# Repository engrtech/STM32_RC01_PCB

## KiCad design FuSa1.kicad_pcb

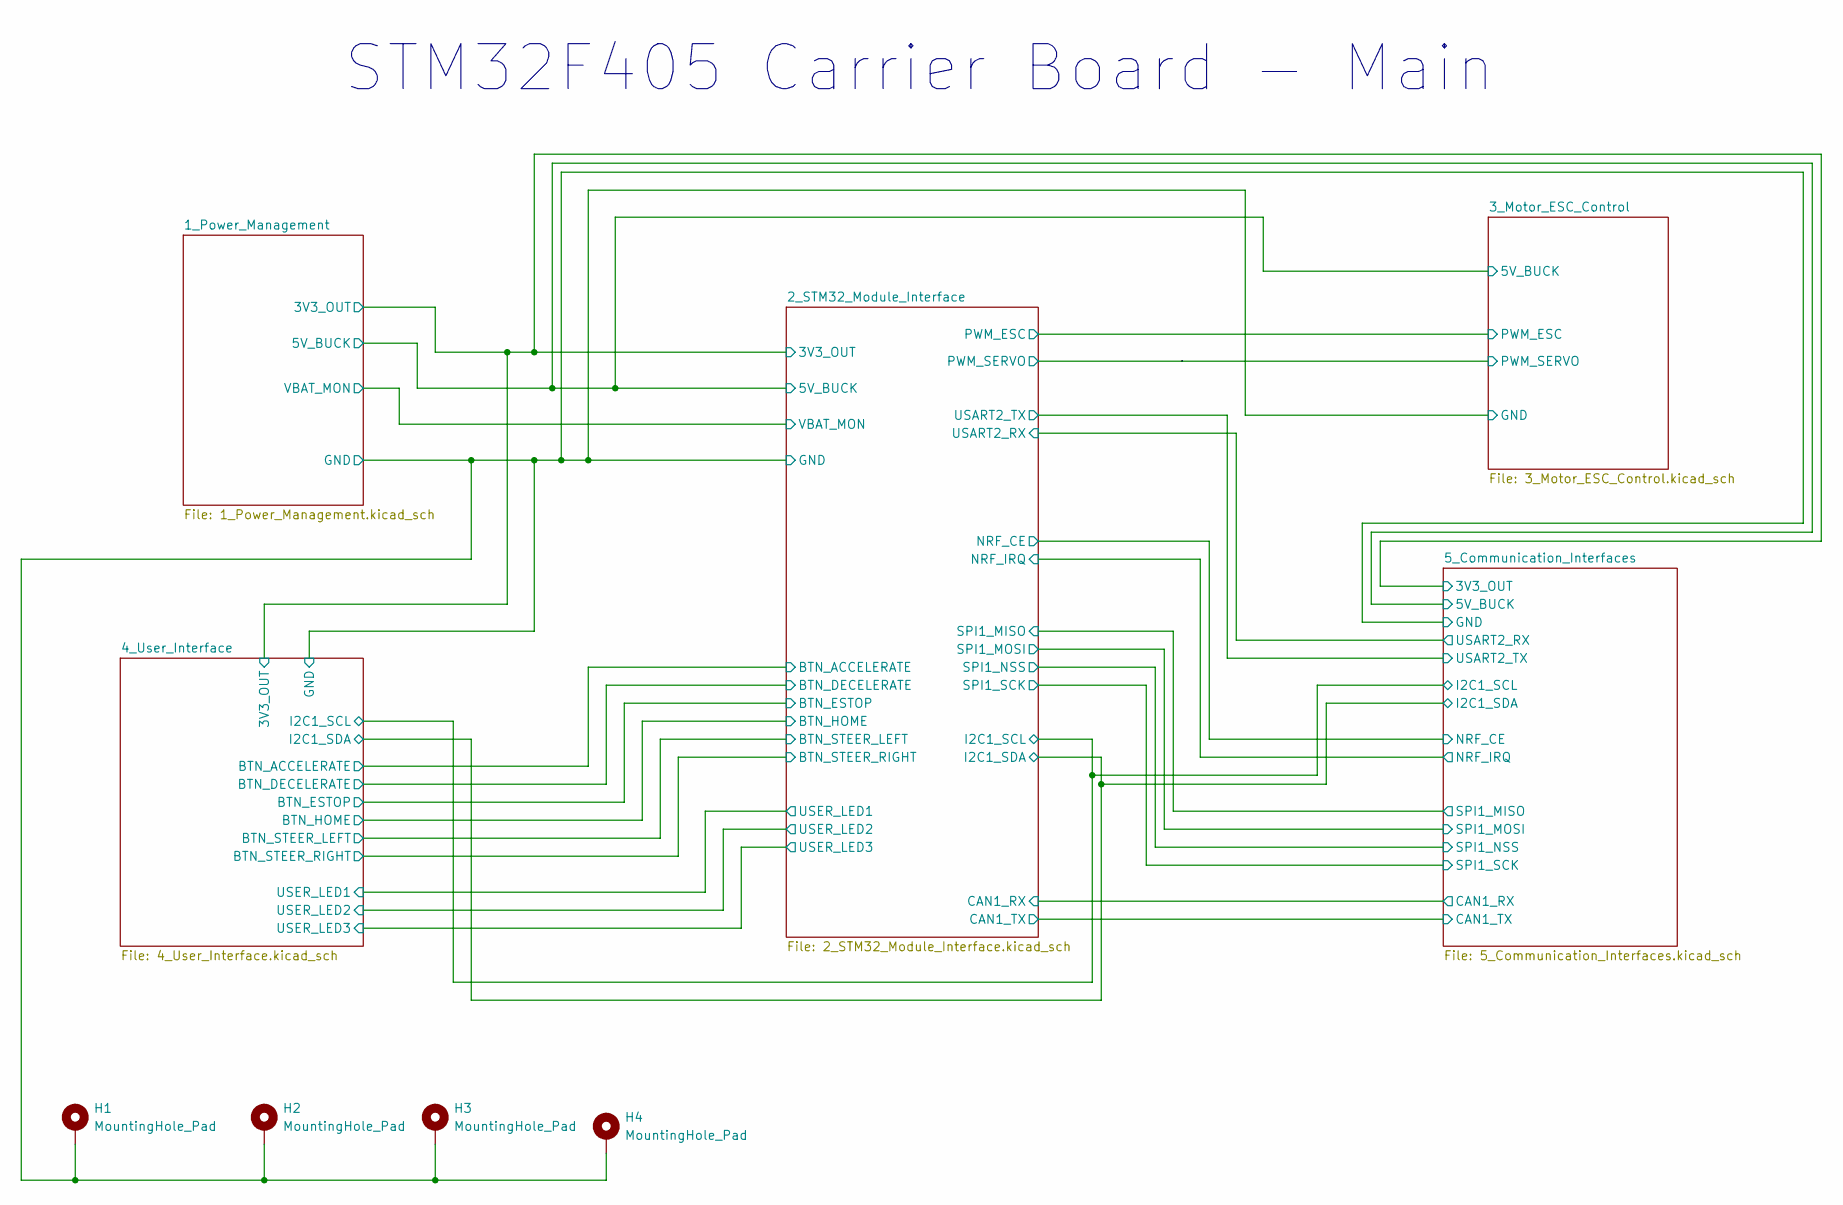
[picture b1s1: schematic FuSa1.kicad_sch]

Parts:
H1, H2, H3, H4: MountingHole_Pad; MountingHole_3.2mm_M3_Pad

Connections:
/1_Power_Management/GND: H1.1, H2.1, H3.1, H4.1; also elsewhere on the board

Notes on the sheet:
STM32F405 Carrier Board - Main

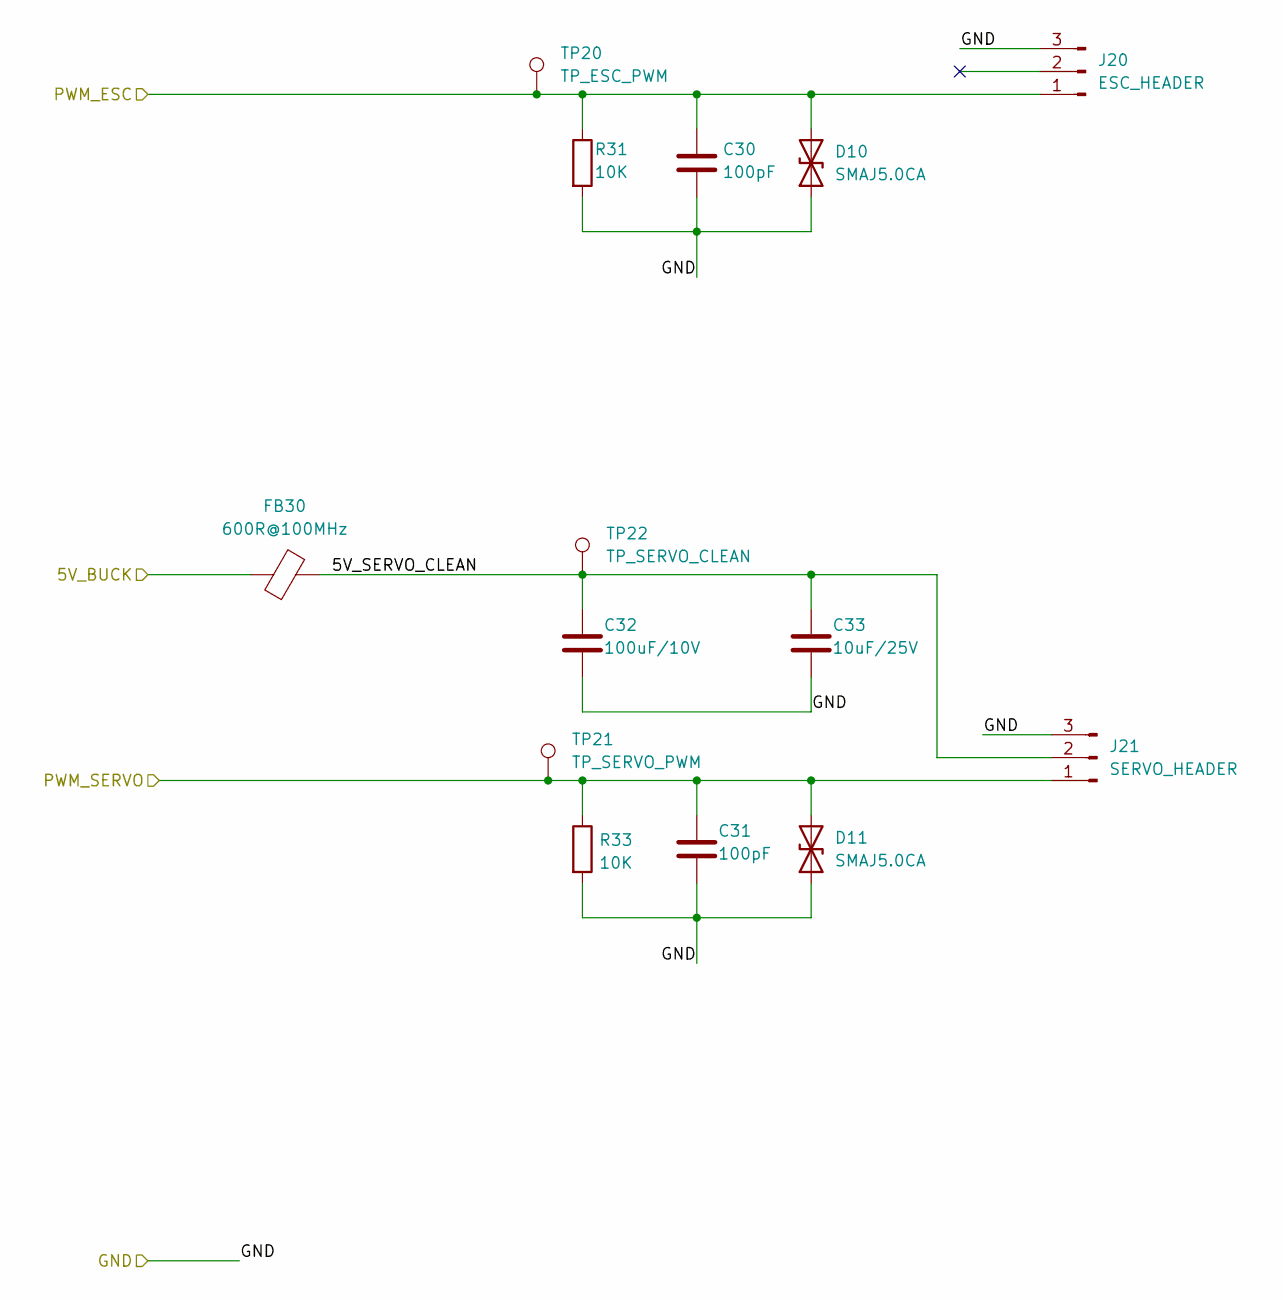
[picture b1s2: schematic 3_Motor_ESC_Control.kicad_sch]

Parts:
C30, C31: 100pF; C_0603_1608Metric; LCSC C14858
C32: 100uF/10V; CP_Radial_D5.0mm_P2.00mm; LCSC C83646
C33: 10uF/25V; C_0603_1608Metric; LCSC C6119815
D10, D11: SMAJ5.0CA; D_SMA; LCSC C83324
FB30: 600R@100MHz; L_1206_3216Metric; LCSC C16902
J20: ESC_HEADER; PinHeader_1x03_P2.54mm_Vertical
J21: SERVO_HEADER; PinHeader_1x03_P2.54mm_Vertical
R31, R33: 10K; R_0603_1608Metric; LCSC C15401
TP20: TP_ESC_PWM; TestPoint_Pad_D2.0mm
TP21: TP_SERVO_PWM; TestPoint_Pad_D2.0mm
TP22: TP_SERVO_CLEAN; TestPoint_Pad_D2.0mm

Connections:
/1_Power_Management/5V_BUCK: FB30.1; also elsewhere on the board
/1_Power_Management/GND: C30.2, C31.2, C32.2, C33.2, D10.1 (A1), D11.1 (A1), J20.3, J21.3, R31.2, R33.2; also elsewhere on the board
/2_STM32_Module_Interface/PWM_ESC: C30.1, D10.2 (A2), J20.1, R31.1, TP20.1; also elsewhere on the board
/2_STM32_Module_Interface/PWM_SERVO: C31.1, D11.2 (A2), J21.1, R33.1, TP21.1; also elsewhere on the board
/3_Motor_ESC_Control/5V_SERVO_CLEAN: C32.1, C33.1, FB30.2, J21.2, TP22.1

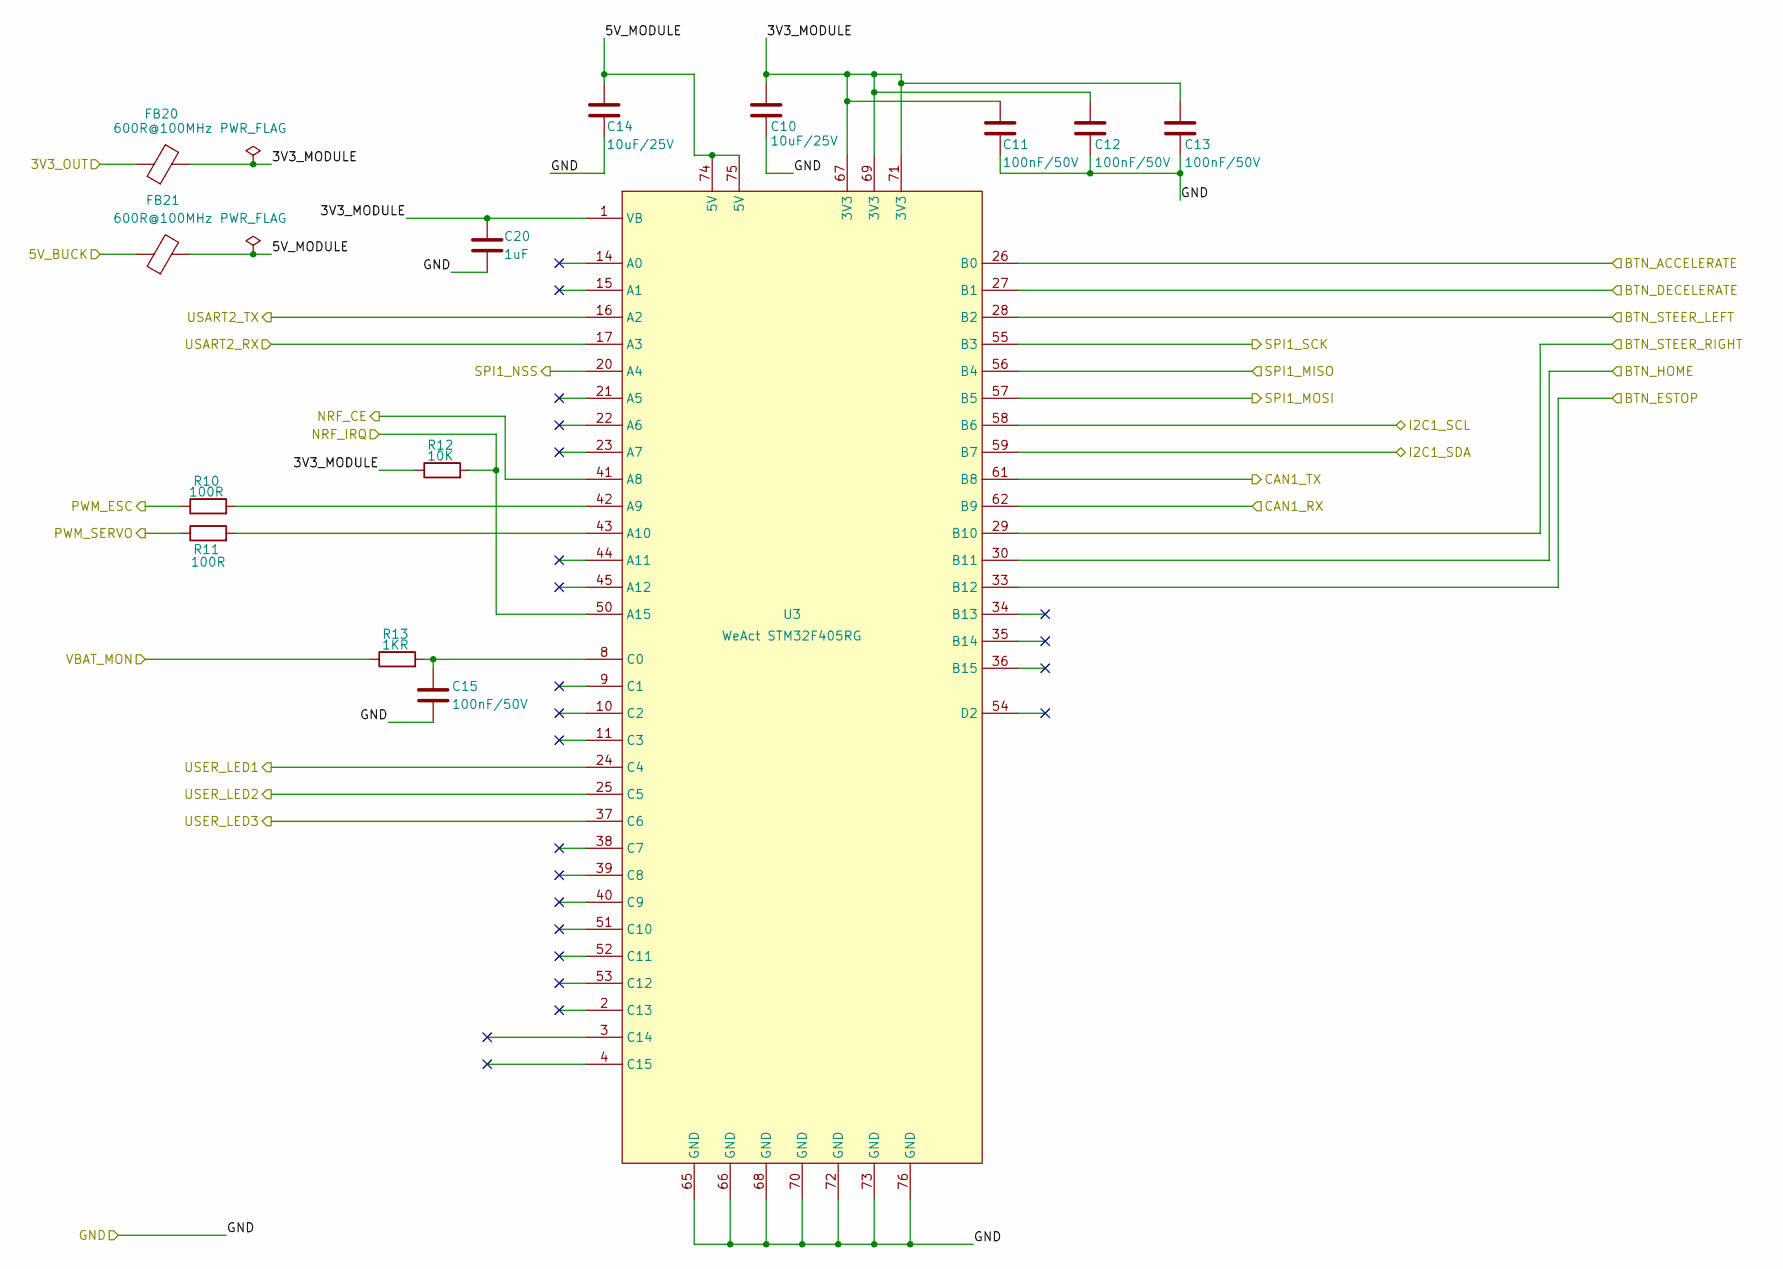
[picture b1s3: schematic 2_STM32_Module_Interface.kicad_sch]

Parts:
C10, C14: 10uF/25V; C_0603_1608Metric; LCSC C6119815
C11, C12, C13, C15: 100nF/50V; C_0603_1608Metric; LCSC C6119867
C20: 1uF; C_0603_1608Metric; LCSC C5199872
FB20, FB21: 600R@100MHz; L_1206_3216Metric; LCSC C16902
R10, R11: 100R; R_0603_1608Metric; LCSC C17901
R12: 10K; R_0603_1608Metric; LCSC C15401
R13: 1KR; R_0603_1608Metric; LCSC C14676
U3: WeAct STM32F405RG; WeAct_STM32F405

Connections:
/1_Power_Management/5V_BUCK: FB21.1; also elsewhere on the board
/1_Power_Management/GND: C10.2, C11.2, C12.2, C13.2, C14.2, C15.2, C20.1, U3.65 (GND), U3.66 (GND), U3.68 (GND), U3.70 (GND), U3.72 (GND), U3.73 (GND), U3.76 (GND); also elsewhere on the board
/1_Power_Management/VBAT_MON: R13.1; also elsewhere on the board
/2_STM32_Module_Interface/3V3_MODULE: C10.1, C11.1, C12.1, C13.1, C20.2, FB20.2, R12.1, U3.1 (VB), U3.67 (3V3), U3.69 (3V3), U3.71 (3V3)
/2_STM32_Module_Interface/5V_MODULE: C14.1, FB21.2, U3.74 (5V), U3.75 (5V)
/2_STM32_Module_Interface/BTN_ACCELERATE: U3.26 (B0); also elsewhere on the board
/2_STM32_Module_Interface/BTN_DECELERATE: U3.27 (B1); also elsewhere on the board
/2_STM32_Module_Interface/BTN_ESTOP: U3.33 (B12); also elsewhere on the board
/2_STM32_Module_Interface/BTN_HOME: U3.30 (B11); also elsewhere on the board
/2_STM32_Module_Interface/BTN_STEER_LEFT: U3.28 (B2); also elsewhere on the board
/2_STM32_Module_Interface/BTN_STEER_RIGHT: U3.29 (B10); also elsewhere on the board
/2_STM32_Module_Interface/CAN1_RX: U3.62 (B9); also elsewhere on the board
/2_STM32_Module_Interface/CAN1_TX: U3.61 (B8); also elsewhere on the board
/2_STM32_Module_Interface/NRF_CE: U3.41 (A8); also elsewhere on the board
/2_STM32_Module_Interface/NRF_IRQ: R12.2, U3.50 (A15); also elsewhere on the board
/2_STM32_Module_Interface/PWM_ESC: R10.1; also elsewhere on the board
/2_STM32_Module_Interface/PWM_SERVO: R11.1; also elsewhere on the board
/2_STM32_Module_Interface/SPI1_MISO: U3.56 (B4); also elsewhere on the board
/2_STM32_Module_Interface/SPI1_MOSI: U3.57 (B5); also elsewhere on the board
/2_STM32_Module_Interface/SPI1_NSS: U3.20 (A4); also elsewhere on the board
/2_STM32_Module_Interface/SPI1_SCK: U3.55 (B3); also elsewhere on the board
/2_STM32_Module_Interface/USER_LED1: U3.24 (C4); also elsewhere on the board
/2_STM32_Module_Interface/USER_LED2: U3.25 (C5); also elsewhere on the board
/2_STM32_Module_Interface/USER_LED3: U3.37 (C6); also elsewhere on the board
/4_User_Interface/3V3_OUT: FB20.1; also elsewhere on the board
/4_User_Interface/I2C1_SCL: U3.58 (B6); also elsewhere on the board
/4_User_Interface/I2C1_SDA: U3.59 (B7); also elsewhere on the board
/5_Communication_Interfaces/USART2_RX: U3.17 (A3); also elsewhere on the board
/5_Communication_Interfaces/USART2_TX: U3.16 (A2); also elsewhere on the board
unnamed: R10.2, U3.42 (A9)
unnamed: R11.2, U3.43 (A10)
unnamed: C15.1, R13.2, U3.8 (C0)

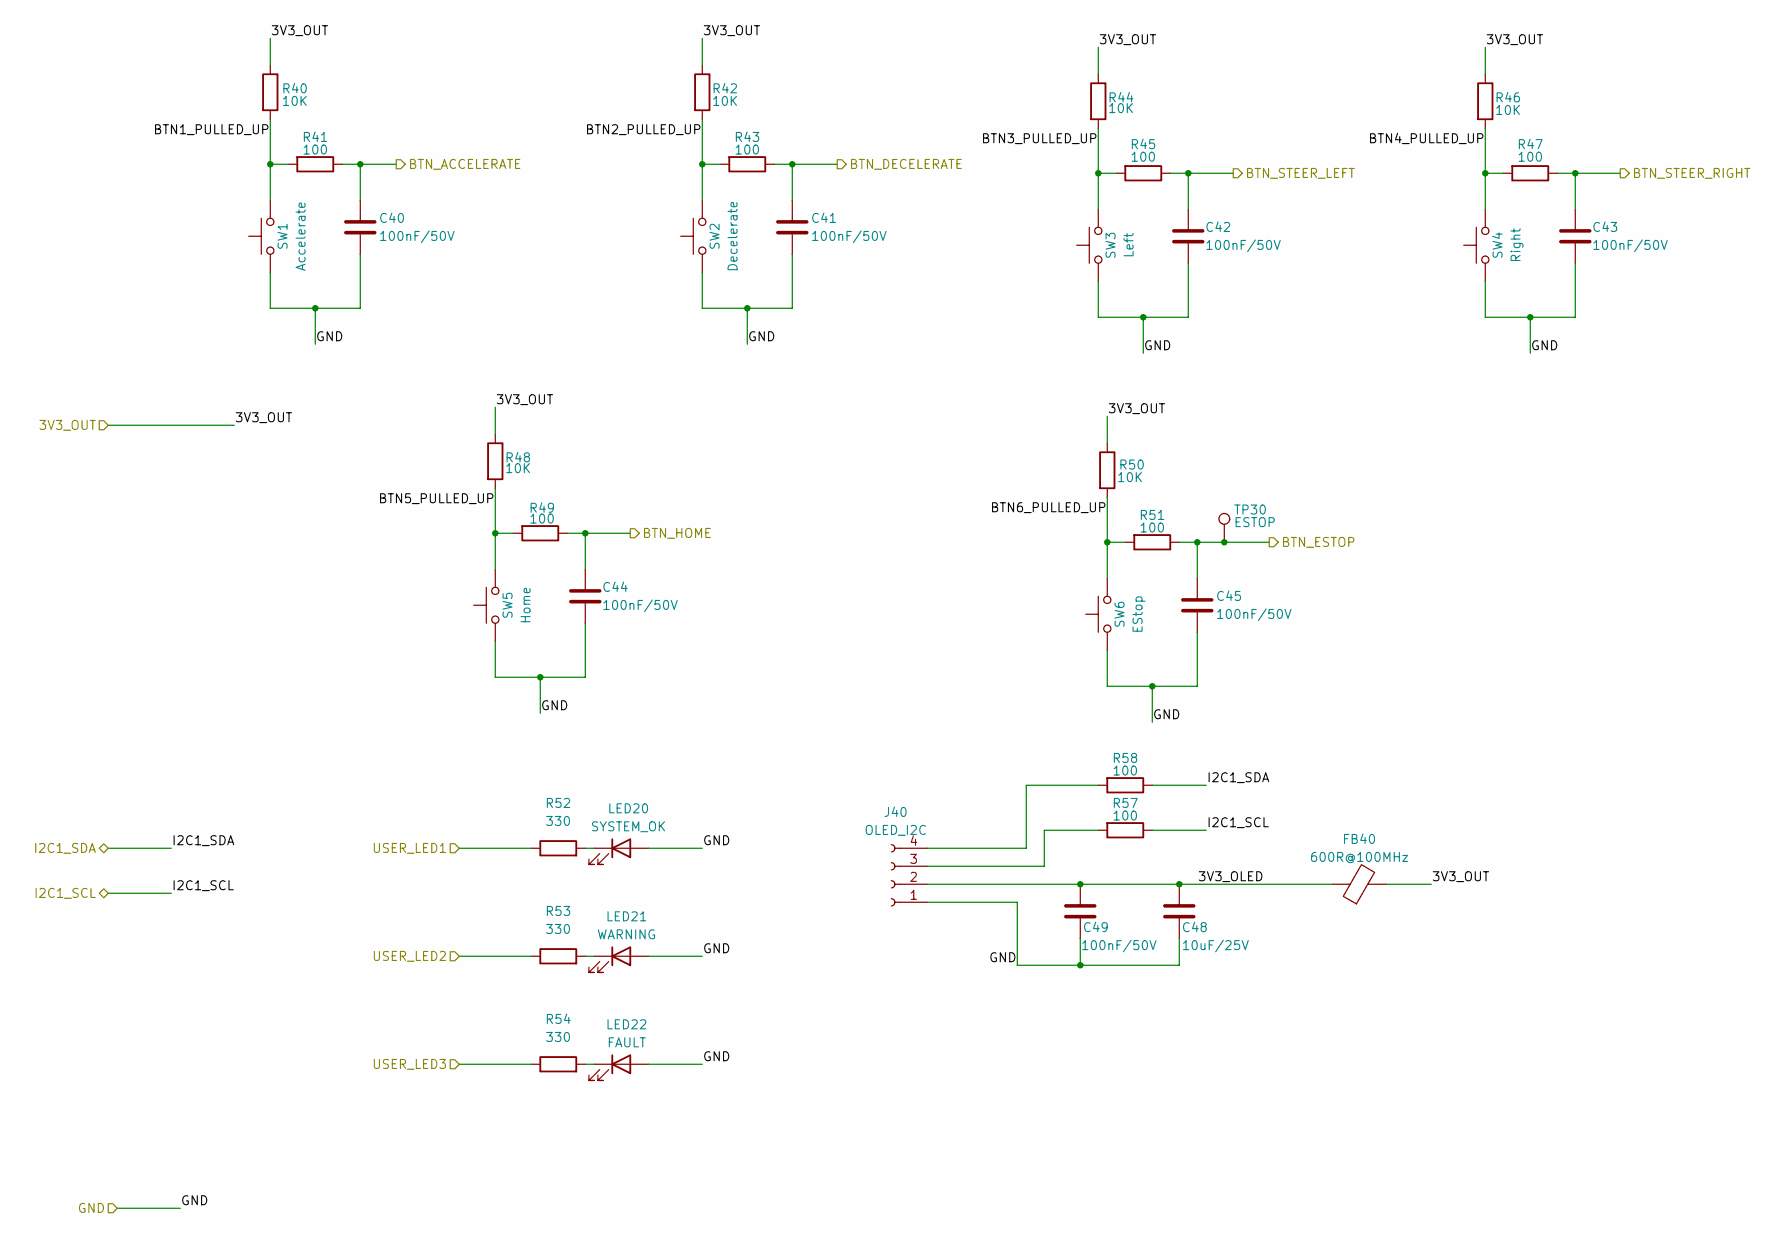
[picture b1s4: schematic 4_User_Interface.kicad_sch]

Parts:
C40, C41, C42, C43, C44, C45, C49: 100nF/50V; C_0603_1608Metric; LCSC C6119867
C48: 10uF/25V; C_0603_1608Metric; LCSC C6119815
FB40: 600R@100MHz; L_1206_3216Metric; LCSC C16902
J40: OLED_I2C; PinHeader_1x04_P2.54mm_Vertical; LCSC C124421
LED20: SYSTEM_OK; LED_1206_3216Metric; LCSC C434439
LED21: WARNING; LED_1206_3216Metric; LCSC C264322
LED22: FAULT; LED_1206_3216Metric; LCSC C559117
R40, R42, R44, R46, R48, R50: 10K; R_0603_1608Metric; LCSC C15401
R41, R43, R45, R47, R49, R51, R57, R58: 100; R_0603_1608Metric; LCSC C22775
R52, R53, R54: 330; R_0603_1608Metric; LCSC C22104
SW1: Accelerate; SW_SPST_B3U-1000P; LCSC C318884
SW2: Decelerate; SW_SPST_B3U-1000P; LCSC C318884
SW3: Left; SW_SPST_B3U-1000P; LCSC C318884
SW4: Right; SW_SPST_B3U-1000P; LCSC C318884
SW5: Home; SW_SPST_B3U-1000P; LCSC C318884
SW6: EStop; SW_SPST_B3U-1000P; LCSC C318884
TP30: ESTOP; TestPoint_Pad_D2.0mm

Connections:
/1_Power_Management/GND: C40.2, C41.2, C42.2, C43.2, C44.2, C45.2, C48.2, C49.2, J40.1, LED20.2 (A), LED21.2 (A), LED22.2 (A), SW1.1, SW2.1, SW3.1, SW4.1, SW5.1, SW6.1; also elsewhere on the board
/2_STM32_Module_Interface/BTN_ACCELERATE: C40.1, R41.1; also elsewhere on the board
/2_STM32_Module_Interface/BTN_DECELERATE: C41.1, R43.1; also elsewhere on the board
/2_STM32_Module_Interface/BTN_ESTOP: C45.1, R51.1, TP30.1; also elsewhere on the board
/2_STM32_Module_Interface/BTN_HOME: C44.1, R49.1; also elsewhere on the board
/2_STM32_Module_Interface/BTN_STEER_LEFT: C42.1, R45.1; also elsewhere on the board
/2_STM32_Module_Interface/BTN_STEER_RIGHT: C43.1, R47.1; also elsewhere on the board
/2_STM32_Module_Interface/USER_LED1: R52.1; also elsewhere on the board
/2_STM32_Module_Interface/USER_LED2: R53.1; also elsewhere on the board
/2_STM32_Module_Interface/USER_LED3: R54.1; also elsewhere on the board
/4_User_Interface/3V3_OLED: C48.1, C49.1, FB40.1, J40.2
/4_User_Interface/3V3_OUT: FB40.2, R40.1, R42.1, R44.1, R46.1, R48.1, R50.1; also elsewhere on the board
/4_User_Interface/BTN1_PULLED_UP: R40.2, R41.2, SW1.2
/4_User_Interface/BTN2_PULLED_UP: R42.2, R43.2, SW2.2
/4_User_Interface/BTN3_PULLED_UP: R44.2, R45.2, SW3.2
/4_User_Interface/BTN4_PULLED_UP: R46.2, R47.2, SW4.2
/4_User_Interface/BTN5_PULLED_UP: R48.2, R49.2, SW5.2
/4_User_Interface/BTN6_PULLED_UP: R50.2, R51.2, SW6.2
/4_User_Interface/I2C1_SCL: R57.1; also elsewhere on the board
/4_User_Interface/I2C1_SDA: R58.1; also elsewhere on the board
unnamed: J40.3, R57.2
unnamed: J40.4, R58.2
unnamed: LED20.1 (K), R52.2
unnamed: LED21.1 (K), R53.2
unnamed: LED22.1 (K), R54.2

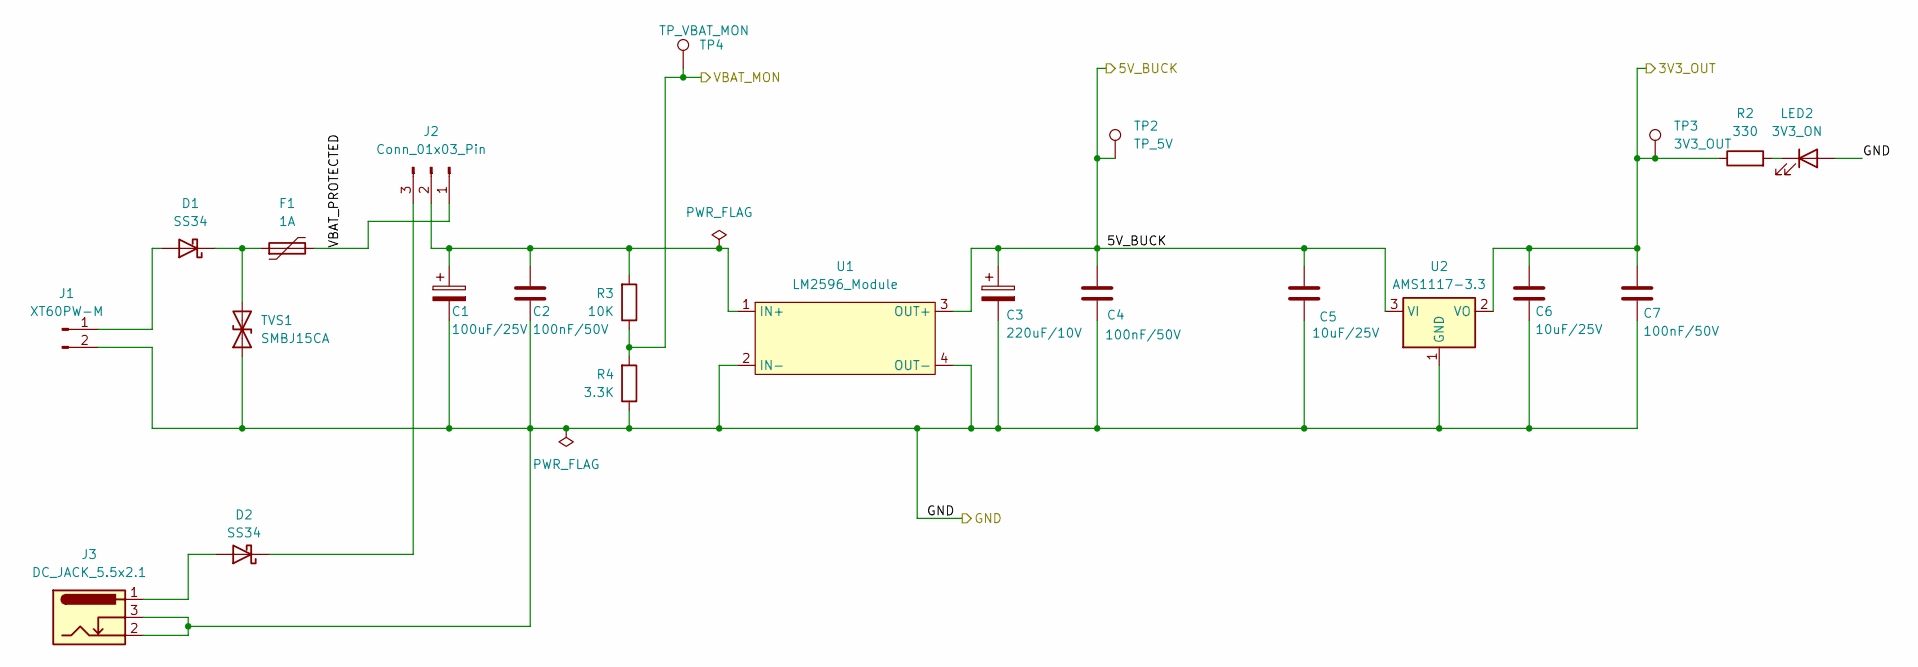
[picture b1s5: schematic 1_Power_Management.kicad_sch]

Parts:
C1: 100uF/25V; CP_Radial_D6.3mm_P2.50mm; LCSC C47250
C2, C4, C7: 100nF/50V; C_0603_1608Metric; LCSC C6119867
C3: 220uF/10V; CP_Radial_D8.0mm_P3.50mm; LCSC C47262
C5, C6: 10uF/25V; C_0603_1608Metric; LCSC C6119815
D1, D2: SS34; D_SMA; LCSC C8678
F1: 1A; Fuse_1206_3216Metric; LCSC C19078717
J1: XT60PW-M; AMASS_XT60PW-M_1x02_P7.20mm_Horizontal; LCSC C2962205
J2: Conn_01x03_Pin; PinHeader_1x03_P2.54mm_Vertical
J3: DC_JACK_5.5x2.1; BarrelJack_Horizontal; LCSC C720560
LED2: 3V3_ON; LED_1206_3216Metric; LCSC C434439
R2: 330; R_0603_1608Metric; LCSC C22104
R3: 10K; R_0603_1608Metric; LCSC C15401
R4: 3.3K; R_0603_1608Metric; LCSC C22978
TP2: TP_5V; TestPoint_Pad_D2.0mm
TP3: 3V3_OUT; TestPoint_Pad_D2.0mm
TP4: TP_VBAT_MON; TestPoint_Pad_D2.0mm
TVS1: SMBJ15CA; D_SMB; LCSC C78809
U1: LM2596_Module
U2: AMS1117-3.3; SOT-223-3_TabPin2; LCSC C6186

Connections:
/1_Power_Management/5V_BUCK: C3.1, C4.1, C5.1, TP2.1, U1.3 (OUT+), U2.3 (VI); also elsewhere on the board
/1_Power_Management/GND: C1.2, C2.2, C3.2, C4.2, C5.2, C6.2, C7.2, J1.2, J3.2, J3.3, LED2.2 (A), R4.1, TVS1.1 (A1), U1.2 (IN-), U1.4 (OUT-), U2.1 (GND); also elsewhere on the board
/1_Power_Management/VBAT_MON: R3.1, R4.2, TP4.1; also elsewhere on the board
/1_Power_Management/VBAT_PROTECTED: F1.2, J2.1
/4_User_Interface/3V3_OUT: C6.1, C7.1, R2.1, TP3.1, U2.2 (VO); also elsewhere on the board
unnamed: D1.2 (A), J1.1
unnamed: D1.1 (K), F1.1, TVS1.2 (A2)
unnamed: D2.2 (A), J3.1
unnamed: D2.1 (K), J2.3
unnamed: C1.1, C2.1, J2.2, R3.2, U1.1 (IN+)
unnamed: LED2.1 (K), R2.2

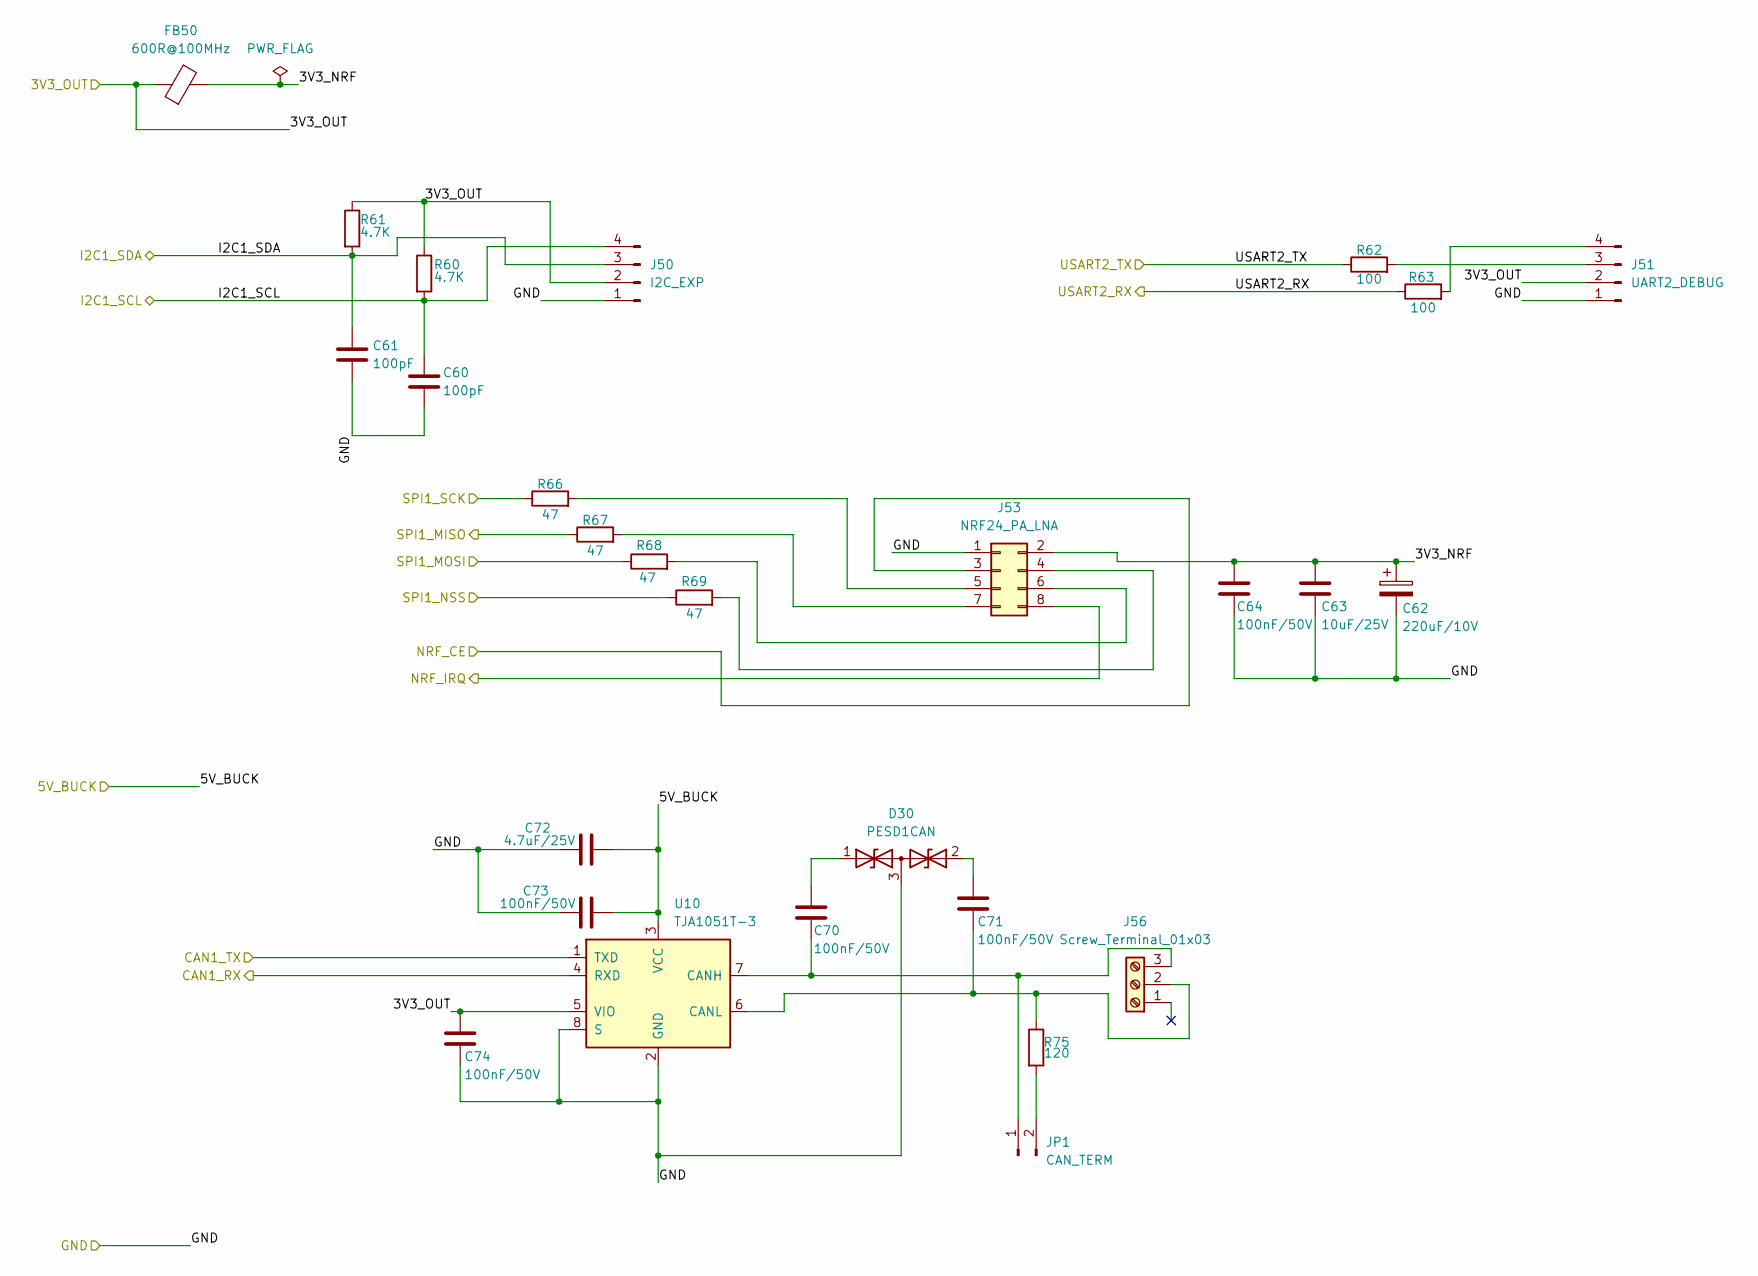
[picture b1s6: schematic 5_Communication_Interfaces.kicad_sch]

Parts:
C60, C61: 100pF; C_0603_1608Metric; LCSC C14858
C62: 220uF/10V; CP_Radial_D6.3mm_P2.50mm; LCSC C47262
C63: 10uF/25V; C_0603_1608Metric; LCSC C6119815
C64, C70, C71, C73, C74: 100nF/50V; C_0603_1608Metric; LCSC C6119867
C72: 4.7uF/25V; C_0603_1608Metric; LCSC C90057
D30: PESD1CAN; SOT-23; LCSC C2827654
FB50: 600R@100MHz; L_1206_3216Metric; LCSC C16902
J50: I2C_EXP; PinSocket_1x04_P2.54mm_Vertical; LCSC C124421
J51: UART2_DEBUG; PinSocket_1x04_P2.54mm_Vertical; LCSC C124421
J53: NRF24_PA_LNA; PinSocket_2x04_P2.54mm_Vertical
J56: Screw_Terminal_01x03; TerminalBlock_Phoenix_MKDS-1,5-3_1x03_P5.00mm_Horizontal; LCSC C395850
JP1: CAN_TERM; PinHeader_1x02_P2.54mm_Vertical
R60, R61: 4.7K; R_0603_1608Metric; LCSC C23162
R62, R63: 100; R_0603_1608Metric; LCSC C22775
R66, R67, R68, R69: 47; R_0603_1608Metric; LCSC C1211
R75: 120; R_0603_1608Metric; LCSC C114640
U10: TJA1051T-3; SOIC-8_3.9x4.9mm_P1.27mm; LCSC C38695

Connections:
/1_Power_Management/5V_BUCK: C72.2, C73.1, U10.3 (VCC); also elsewhere on the board
/1_Power_Management/GND: C60.2, C61.2, C62.2, C63.2, C64.2, C72.1, C73.2, C74.1, D30.3 (common), J50.1, J51.1, J53.1, U10.2 (GND), U10.8 (S); also elsewhere on the board
/2_STM32_Module_Interface/CAN1_RX: U10.4 (RXD); also elsewhere on the board
/2_STM32_Module_Interface/CAN1_TX: U10.1 (TXD); also elsewhere on the board
/2_STM32_Module_Interface/NRF_CE: J53.3; also elsewhere on the board
/2_STM32_Module_Interface/NRF_IRQ: J53.8; also elsewhere on the board
/2_STM32_Module_Interface/SPI1_MISO: R67.1; also elsewhere on the board
/2_STM32_Module_Interface/SPI1_MOSI: R68.1; also elsewhere on the board
/2_STM32_Module_Interface/SPI1_NSS: R69.1; also elsewhere on the board
/2_STM32_Module_Interface/SPI1_SCK: R66.1; also elsewhere on the board
/4_User_Interface/3V3_OUT: C74.2, FB50.1, J50.2, J51.2, R60.1, R61.1, U10.5 (VIO); also elsewhere on the board
/4_User_Interface/I2C1_SCL: C60.1, J50.4, R60.2; also elsewhere on the board
/4_User_Interface/I2C1_SDA: C61.1, J50.3, R61.2; also elsewhere on the board
/5_Communication_Interfaces/3V3_NRF: C62.1, C63.1, C64.1, FB50.2, J53.2
/5_Communication_Interfaces/USART2_RX: R63.1; also elsewhere on the board
/5_Communication_Interfaces/USART2_TX: R62.1; also elsewhere on the board
unnamed: C70.1, D30.1 (A1)
unnamed: C71.1, D30.2 (A2)
unnamed: J51.3, R62.2
unnamed: J51.4, R63.2
unnamed: J53.4, R69.2
unnamed: J53.5, R66.2
unnamed: J53.6, R68.2
unnamed: J53.7, R67.2
unnamed: C71.2, J56.2, R75.1, U10.6 (CANL)
unnamed: C70.2, J56.3, JP1.1, U10.7 (CANH)
unnamed: JP1.2, R75.2

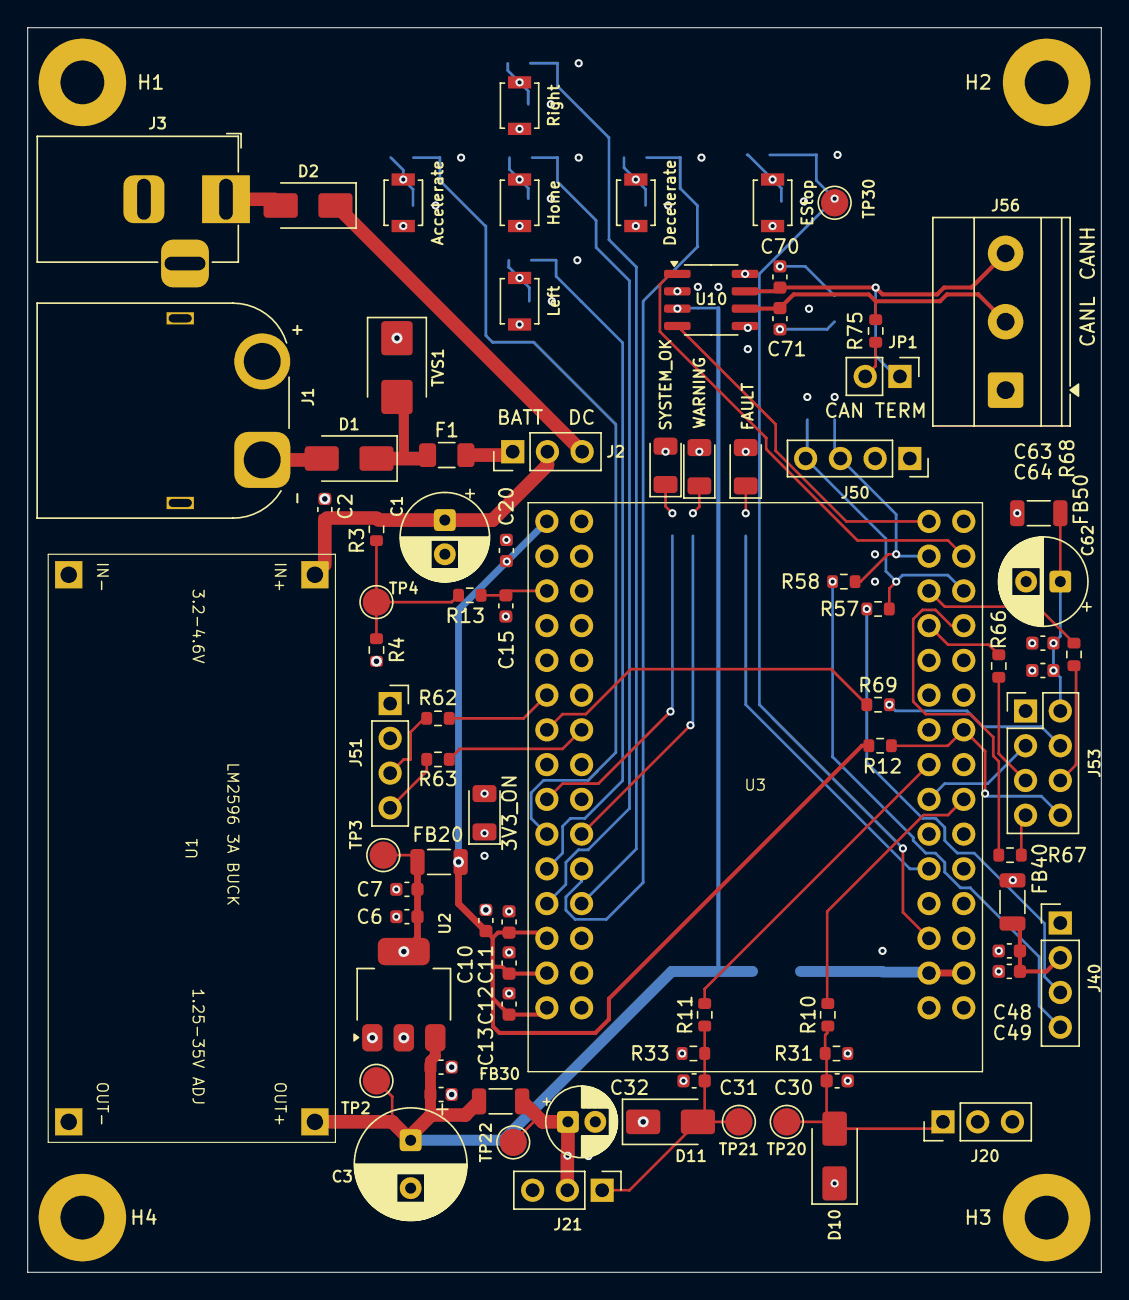
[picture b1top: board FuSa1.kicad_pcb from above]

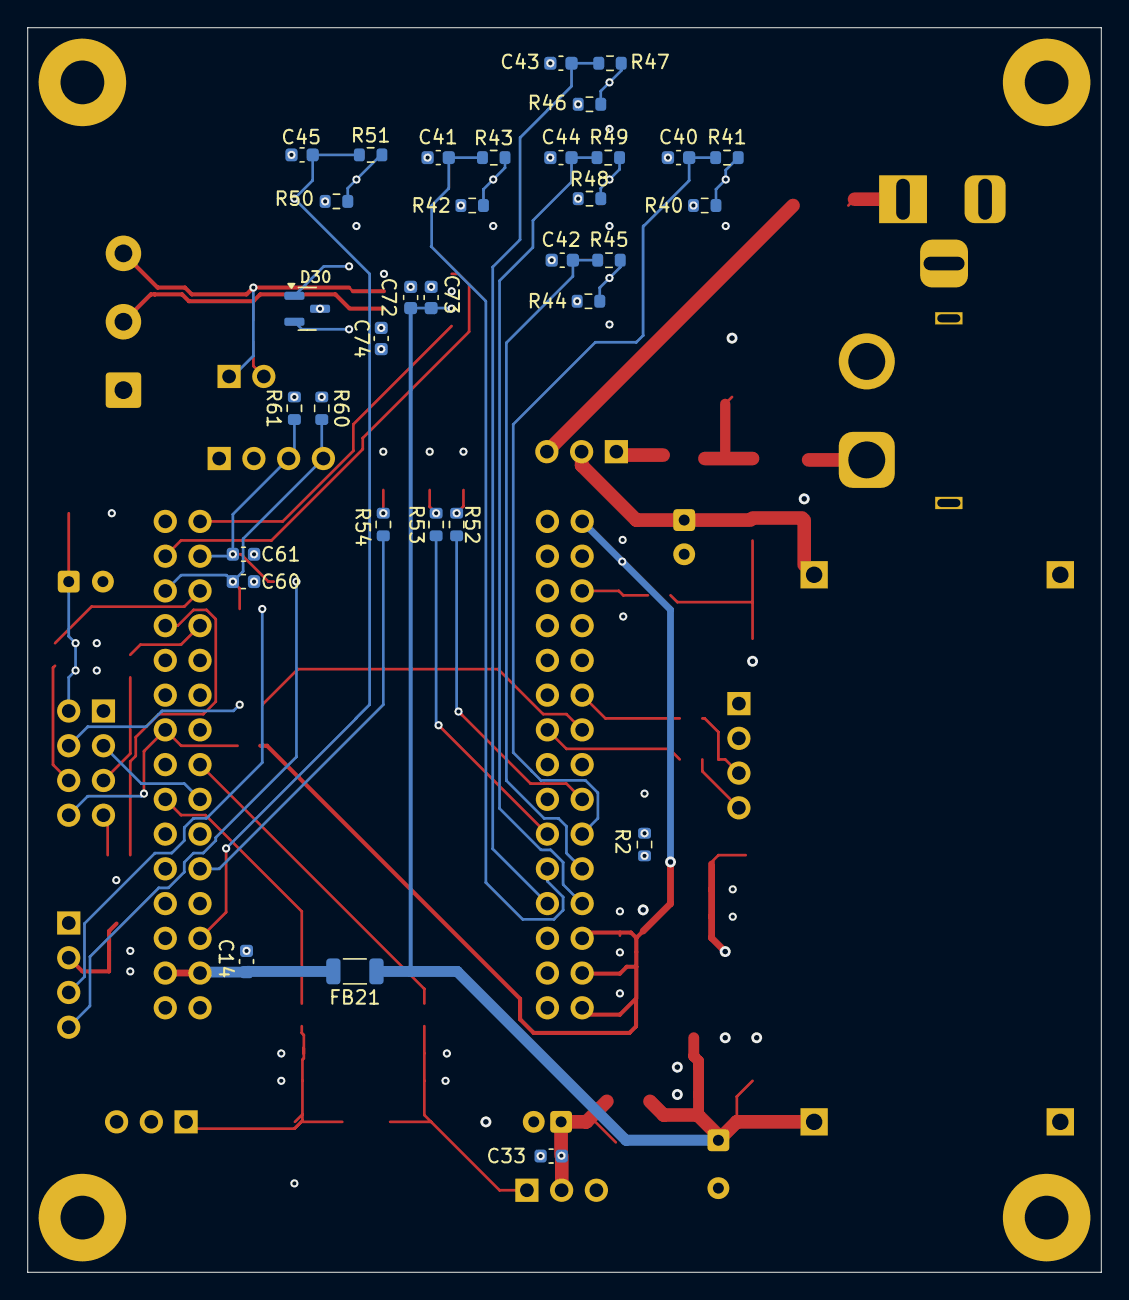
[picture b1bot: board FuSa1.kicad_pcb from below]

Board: 4 copper layers, 78.5 x 91.0 mm, 119 parts (33 on the bottom side), 64 nets.

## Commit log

2025-11-16 Initial commit of full KiCad project
2025-11-19 3D views
2025-11-26 Updated BOM. Initial review and corrections
2025-11-27 Cleaned up schematic. Added mounting holes.
